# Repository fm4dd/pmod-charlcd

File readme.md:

## CharLCD PMOD

### Description

This PMOD interfaces a HD44780-compatible 5V character LCD module via two PMOD connectors. This design connects all 8 data signal lines, and allows to run the LCD in both 4-bit and 8-bit mode. The build-in level converter boosts the 3.3V PMOD power and signal levels to 5V. Its physical size matches LCD modules types such as the Sunlike HUOB-XA-G-G. The additional 7x2 socket can interface with LCD displays using the 7x2 dual-row connector type. The resistor RV1 controls the contrast.

http://fpga.fm4dd.com/

### Schematic

### PCB Gerber

| Version | Gerber | Schema |
|---------|--------|--------|
| 1.0     |[20221207-pmod-charlcd-gerber.zip](fabfiles/v10/20221207-pmod-charlcd-gerber.zip) | [20221207-pmod-charlcd-schema.pdf](fabfiles/v10/20221207-pmod-charlcd-schema.pdf) |

### Pin Assignments

#### IceBreaker v1.0

 J21 |	Label |	Description   |	PMOD1A | J22 |	Label |	Description   | PMOD1B
-----|--------|---------------|--------|-----|--------|---------------|--------
1    |	d[7]  |	LCD Data-7    | 4      |1    |	en    |	LCD EN Signal | 43
2    |	d[5]  |	LCD Data-5    | 2      |2    |	rs    |	LCD RS Signal | 38
3    |	d[3]  |	LCD Data-3    | 47     |3    |	-     |	Not connected | 34
4    |  d[1]  |	LCD Data-1    | 45     |4    |  -     | Not connected | 31
7    |	d[6]  |	LCD Data-6    | 3      |7    |	rw    |	LCD RW Signal | 42
8    |	d[4]  |	LCD Data-4    | 48     |8    |	-     |	Not connected | 36
9    |  d[2]  |	LCD Data-2    |	46     |9    |  -     | Not connected | 32
10   |  d[0]  |	LCD Data-0    |	44     |10   |  -     |	Not connected | 28

### Code Examples

| Board                               | Description                                                       |
|-------------------------------------|-------------------------------------------------------------------|
| [iCEBreaker](examples/icebreaker)   | CharLCD Verilog demo for the iCEBreaker FPGA (Lattice ICE40UP5K)  |
| [Gatemate E1](examples/gatemate) | CharLCD Verilog demo for the Gatemate FPGA (Gatemate CCGM1A1)  |

### Board Pictures

CharLCD PMOD, connected to the iCEBreaker board.

CharLCD PMOD, connected to the Gatemate E1 board.

CharLCD PMOD, connected to the ULX3S board.

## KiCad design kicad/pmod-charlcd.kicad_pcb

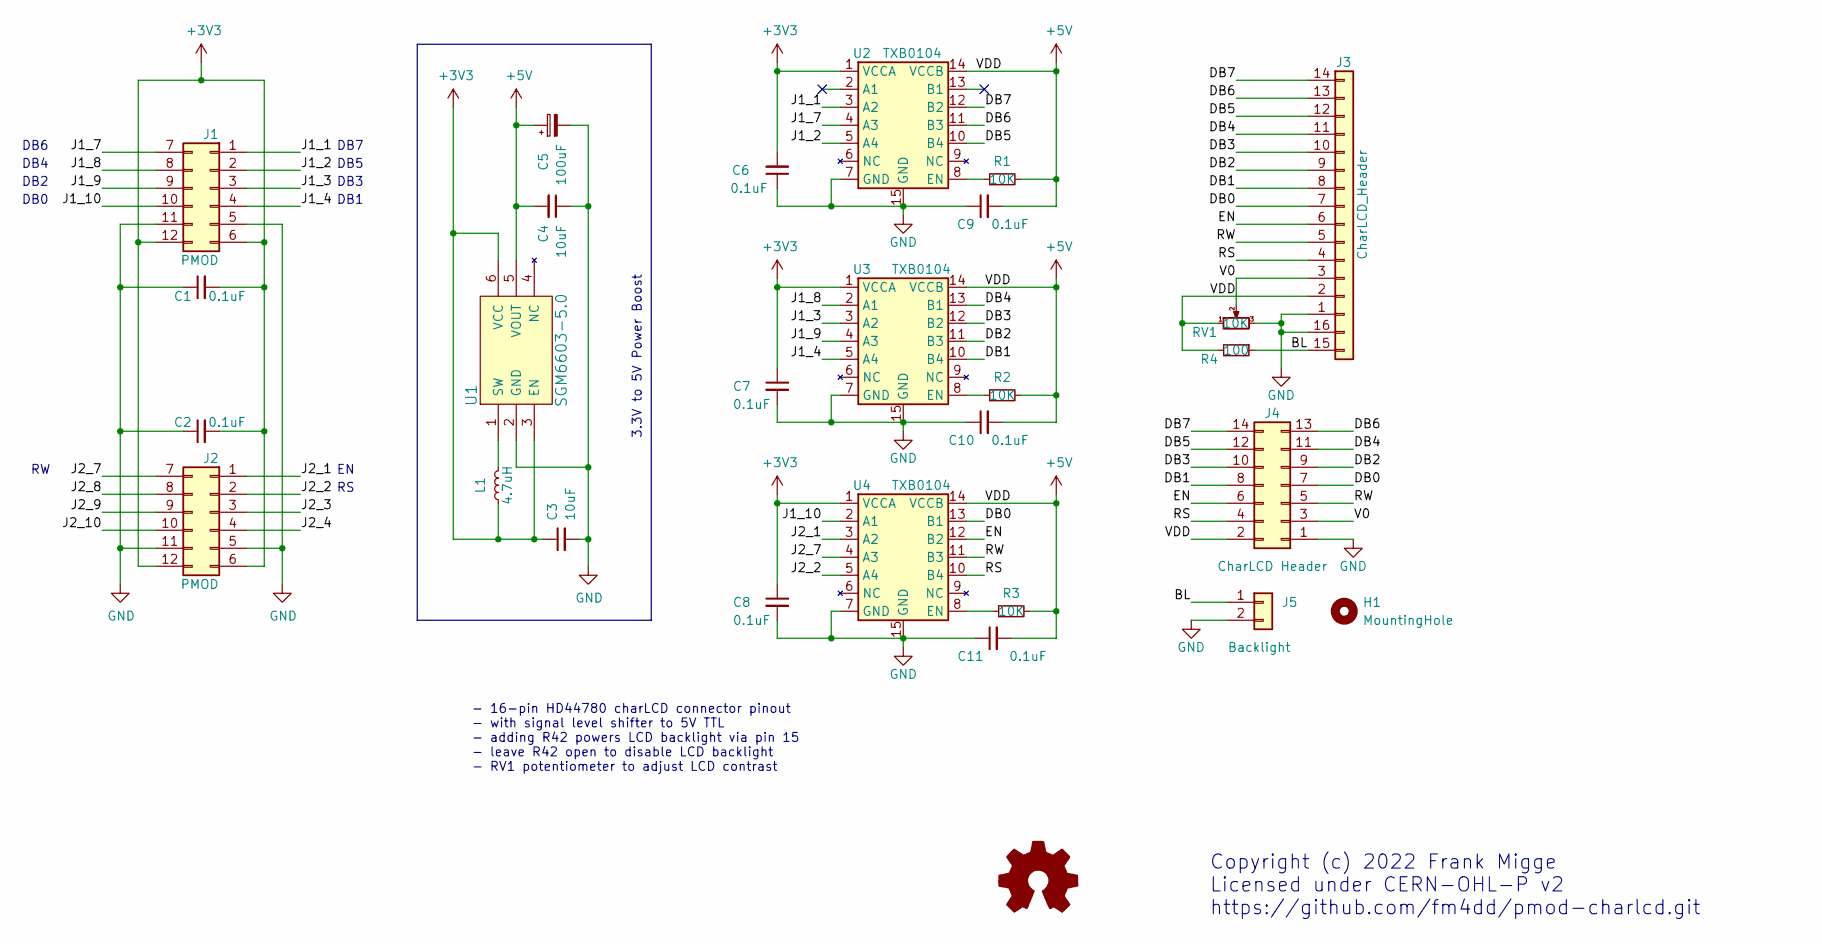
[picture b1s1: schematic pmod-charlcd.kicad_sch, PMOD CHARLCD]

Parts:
C1, C2, C6, C7, C8, C9, C10, C11: 0.1uF; C_0402_1005Metric
C3, C4: 10uF; C_0603_1608Metric
C5: 100uF; CP_Elec_6.3x5.4
H1: MountingHole; MountingHole_2.1mm
J1, J2: PMOD; PMODHeader_2x06_P2.54mm_Horizontal
J3: CharLCD_Header; CharLCD Header HUOB-XA-G-G
J4: CharLCD Header; CharLCD_PinSocket_2x07
J5: Backlight; PinHeader_1x02_P2.54mm_Vertical
L1: 4.7uH; L_0603_1608Metric
R1, R2, R3: 10K; R_0402_1005Metric
R4: 100; R_0402_1005Metric
RV1: 10K; Potentiometer_Bourns_3362P_Vertical
U1: SGM6603-5.0; SOT-23-6
U2, U3, U4: TXB0104; S-PVQFN-N14-1EP_3.65x3.65_P0.5_EP2.05x2.05

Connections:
+3V3: C1.2, C2.2, C3.1, C6.2, C7.1, C8.1, J1.6, J1.12, J2.6, J2.12, L1.1, U1.3 (EN), U1.6 (VCC), U2.1 (VCCA), U3.1 (VCCA), U4.1 (VCCA)
+5V: C4.2, C5.1, C9.2, C10.2, C11.2, J3.2, J4.2, R1.2, R2.2, R3.2, R4.2, RV1.1, U1.5 (VOUT), U2.14 (VCCB), U3.14 (VCCB), U4.14 (VCCB)
/BL: J3.15, J5.1, R4.1
/DB0: J3.7, J4.7, U4.13 (B1)
/DB1: J3.8, J4.8, U3.10 (B4)
/DB2: J3.9, J4.9, U3.11 (B3)
/DB3: J3.10, J4.10, U3.12 (B2)
/DB4: J3.11, J4.11, U3.13 (B1)
/DB5: J3.12, J4.12, U2.10 (B4)
/DB6: J3.13, J4.13, U2.11 (B3)
/DB7: J3.14, J4.14, U2.12 (B2)
/EN: J3.6, J4.6, U4.12 (B2)
/J1_1: J1.1, U2.3 (A2)
/J1_2: J1.2, U2.5 (A4)
/J1_3: J1.3, U3.3 (A2)
/J1_4: J1.4, U3.5 (A4)
/J1_7: J1.7, U2.4 (A3)
/J1_8: J1.8, U3.2 (A1)
/J1_9: J1.9, U3.4 (A3)
/J1_10: J1.10, U4.2 (A1)
/J2_1: J2.1, U4.3 (A2)
/J2_2: J2.2, U4.5 (A4)
/J2_3: J2.3
/J2_4: J2.4
/J2_7: J2.7, U4.4 (A3)
/J2_8: J2.8
/J2_9: J2.9
/J2_10: J2.10
/RS: J3.4, J4.4, U4.10 (B4)
/RW: J3.5, J4.5, U4.11 (B3)
/V0: J3.3, J4.3, RV1.2
GND: C1.1, C2.1, C3.2, C4.1, C5.2, C6.1, C7.2, C8.2, C9.1, C10.1, C11.1, J1.5, J1.11, J2.5, J2.11, J3.1, J3.16, J4.1, J5.2, RV1.3, U1.2 (GND), U2.7 (GND), U2.15 (GND), U3.7 (GND), U3.15 (GND), U4.7 (GND), U4.15 (GND)
unnamed: L1.2, U1.1 (SW)
unnamed: R1.1, U2.8 (EN)
unnamed: R2.1, U3.8 (EN)
unnamed: R3.1, U4.8 (EN)

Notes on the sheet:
DB0
DB2
DB1
DB7
Copyright (c) 2022 Frank Migge Licensed under CERN-OHL-P v2 https://github.com/fm4dd/pmod-charlcd.git
- 16-pin HD44780 charLCD connector pinout - with signal level shifter to 5V TTL - adding R42 powers LCD backlight via pin 15 - leave R42 open to disable LCD backlight - RV1 potentiometer to adjust LCD contrast
3.3V to 5V Power Boost
DB3
DB6
DB4
DB5

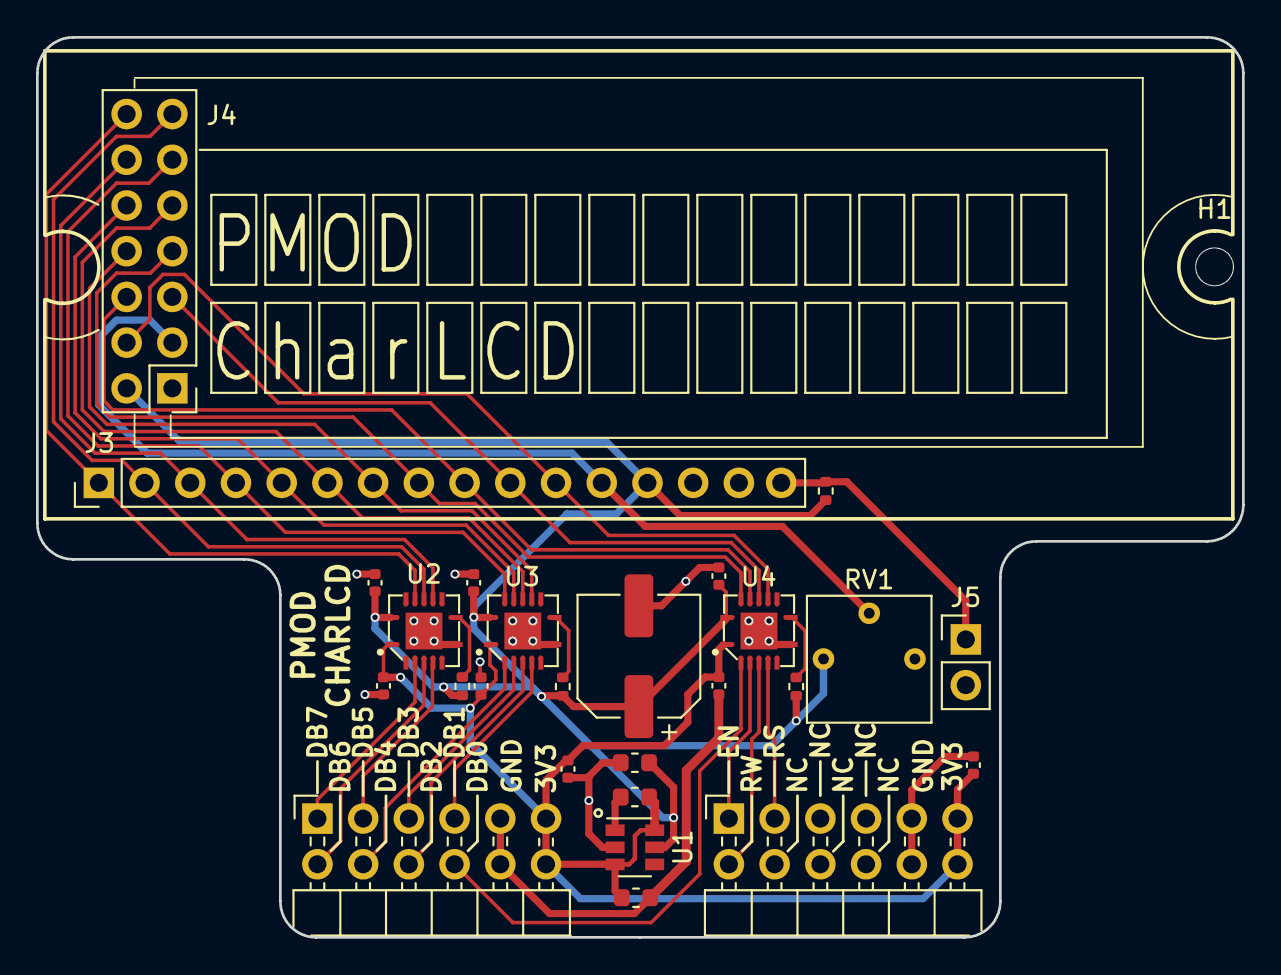
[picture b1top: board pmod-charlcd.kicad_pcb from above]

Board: 2 copper layers, 67.0 x 50.0 mm, 27 parts (0 on the bottom side), 31 nets.

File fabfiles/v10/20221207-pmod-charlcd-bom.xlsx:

Comment | Designator | Footprint | JLCPCB Part #（optional）
0.1u C0402C103K4RECAUTO | C1,C2,C6,C7,C8,C9,C10,C11 | C_0402_1005Metric | C1525
10uF 0402CG150J500NT | C3,C4 | C_0402_1005Metric | C30274
100uF | C5 | CP_Elec_6.3x5.3 | C134749
4.7uH | L1 | L_0603_1608Metric | C1034
SGM6603-5.0 | U1 | SOT-23-6 | C79689
TXB0104 | U2,U3,U4 | S-PVQFN-N14-1EP_3.65x3.65_P0.5_EP2.05x2.05 | C400708
10K | R1,R2,R3 | R_0402_1005Metric | C25744
100 | R4 | R_0402_1005Metric | C25076

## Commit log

2023-01-02 repo init
2023-02-22 fix assignment table pin rw
2023-05-14 add Gatemate example code
2024-02-18 add 2nd LCD example
2024-02-24 add ULX3S example

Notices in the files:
kicad/pmod-charlcd.kicad_pcb:
License: CC-BY-SA 4.0
